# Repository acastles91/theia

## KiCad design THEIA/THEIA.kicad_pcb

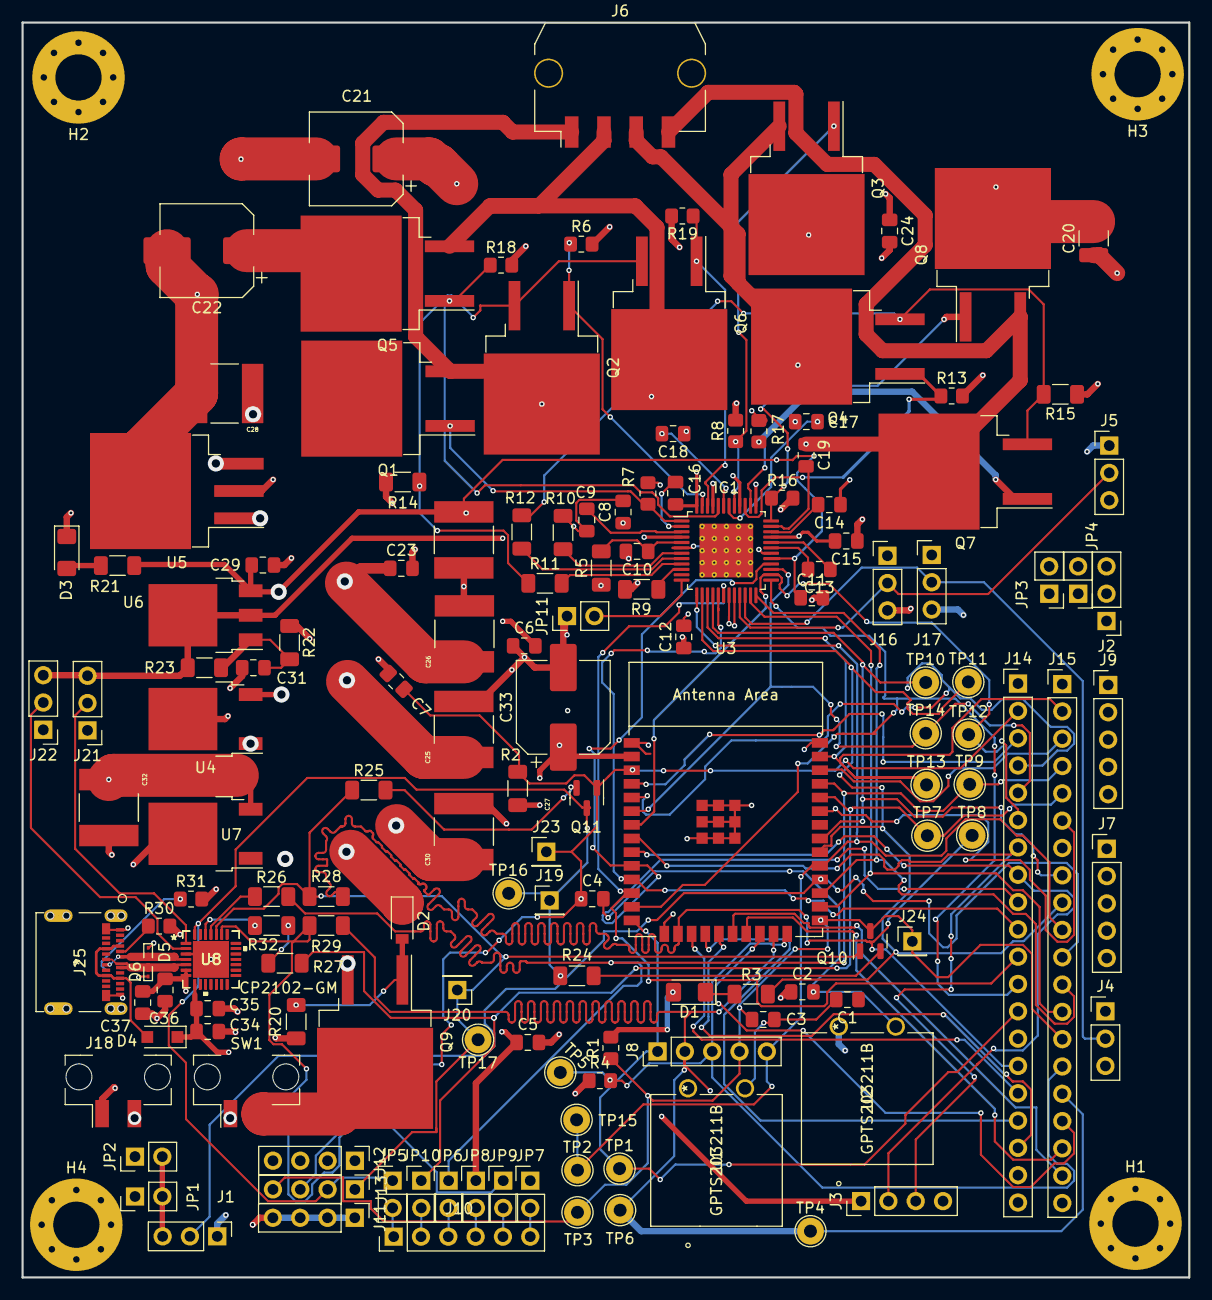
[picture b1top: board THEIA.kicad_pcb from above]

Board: 4 copper layers, 108.5 x 116.7 mm, 154 parts (0 on the bottom side), 103 nets.

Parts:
C1, C2, C6, C8, C12, C14, C15, C16, C17, C18, C19: 0.1uF; C_0805_2012Metric_Pad1.18x1.45mm_HandSolder
C3, C4, C7, C34, C35, C36, C37: 1uF; C_0805_2012Metric_Pad1.18x1.45mm_HandSolder
C5: C22uF; C_0805_2012Metric_Pad1.18x1.45mm_HandSolder
C9, C10: 2.2uF; C_0805_2012Metric_Pad1.18x1.45mm_HandSolder
C11, C23, C24: 0.47uF; C_0805_2012Metric_Pad1.18x1.45mm_HandSolder
C13: 0.022uF; C_0805_2012Metric_Pad1.18x1.45mm_HandSolder
C20: 4.7uF; C_1210_3225Metric_Pad1.33x2.70mm_HandSolder
C21, C22, C33: 22uF; CP_Elec_8x10.5
C25, C26, C27, C28, C30, C32: 22uF; CAPC6153X500N
C29, C31: 10uF; C_0805_2012Metric_Pad1.18x1.45mm_HandSolder
D1, D3: LED_1206_3216Metric_Pad1.42x1.75mm_HandSolder
D2: 10V-Zener; D_SOD-123
D4: 1N5819; D_SOD-123F
D5, D6: ESD9B5.0ST5G; D_SOD-923
H1, H2, H3, H4: MountingHole; MountingHole_4.3mm_M4_Pad_Via
IC1: TMC5160-TA; TQFP-48-1EP_7x7mm_P0.5mm_EP5x5mm_ThermalVias
J1, J2, J4, J5, J21, J22: Conn_01x03_Female; PinHeader_1x03_P2.54mm_Vertical
J3: Conn_01x04_Male; PinHeader_1x04_P2.54mm_Vertical
J6: Conn_01x04_Female; Molex_Micro-Fit_3.0_43650-0410_1x04-1MP_P3.00mm_Horizontal
J7, J9: Conn_01x05_Female; PinHeader_1x05_P2.54mm_Vertical
J8: PinHeader_1x05_P2.54mm_Vertical
J10: PinHeader_1x06_P2.54mm_Vertical
J11, J13: PinHeader_1x04_P2.54mm_Vertical
J12: Conn_01x04_Female; PinHeader_1x04_P2.54mm_Vertical
J14, J15: Conn_01x20_Male; PinHeader_1x20_P2.54mm_Vertical
J16, J17: Conn_01x03_Male; PinHeader_1x03_P2.54mm_Vertical
J18: Conn_01x02_Female; Molex_Micro-Fit_3.0_43650-0221_1x02_P3.00mm_Vertical
J19, J20, J23, J24: PinHeader_1x01_P2.54mm_Vertical
J25: 1054500101
JP1, JP2, JP3, JP4, JP6, JP7, JP8, JP9, JP10, JP11: Jumper_2_Bridged; PinHeader_1x02_P2.54mm_Vertical
JP5: PinHeader_1x02_P2.54mm_Vertical
Q1, Q2, Q3, Q4, Q5, Q6, Q7, Q8: IRLZ44N-SPBF; TO-263-2
Q9: IRF7606PBF; TO-263-2
Q10: S8050; SOT-23
Q11: SOT-23
R1, R4, R30, R31: 5K; R_0805_2012Metric_Pad1.20x1.40mm_HandSolder
R2: R10K; R_1206_3216Metric_Pad1.30x1.75mm_HandSolder
R3: R_1206_3216Metric_Pad1.30x1.75mm_HandSolder
R5: R2.2; R_1206_3216Metric_Pad1.30x1.75mm_HandSolder
R6, R7, R8, R13, R16, R17, R18, R19: R10K; R_0805_2012Metric_Pad1.20x1.40mm_HandSolder
R9, R10, R11, R12: R47; R_1206_3216Metric_Pad1.30x1.75mm_HandSolder
R14, R15: R0.075; R_1206_3216Metric_Pad1.30x1.75mm_HandSolder
R20: R100K; R_1206_3216Metric_Pad1.30x1.75mm_HandSolder
R21: R150K; R_1206_3216Metric_Pad1.30x1.75mm_HandSolder
R22, R26: R0; R_1206_3216Metric_Pad1.30x1.75mm_HandSolder
R23: R3.3K; R_1206_3216Metric_Pad1.30x1.75mm_HandSolder
R24, R25, R32: 10K; R_1206_3216Metric_Pad1.30x1.75mm_HandSolder
R27, R28, R29: 0R; R_1206_3216Metric_Pad1.30x1.75mm_HandSolder
SW1: SW_Push; Molex_Micro-Fit_3.0_43650-0221_1x02_P3.00mm_Vertical
TP1, TP2, TP3, TP4, TP6, TP7, TP8, TP9, TP15: TestPoint; TestPoint_THTPad_D2.5mm_Drill1.2mm
TP5, TP10, TP11, TP12, TP13, TP14, TP16, TP17: TestPoint_THTPad_D2.5mm_Drill1.2mm
U1, U2: GPTS203211B
U3: ESP32-WROOM-E; ESP32-WROOM-32E
U4, U7: TO-252-2
U5: TO-263-3_TabPin2
U6: TO-252-3_TabPin2
U8, U8#2: CP2102-GM

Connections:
5V-LEDS: C32.1, JP2.1 (A), JP4.1 (A), U7.3 (VOUT)
+5V: C11.1, C27.1, C29.1, IC1.29 (VCC), R5.1, R21.2, U4.3 (VOUT), U6.3 (VI)
+12V: C28.1, JP1.1 (A), JP3.1 (A), U5.3 (VOUT)
+24V: C8.1, C14.1, C15.2, C20.2, C21.1, C22.1, C23.1, C24.1, C25.1, C26.1, C30.1, D2.1 (K), IC1.4 (VSA), IC1.33 (VS), Q1.2 (D), Q3.2 (D), Q5.2 (D), Q8.2 (D), Q9.3 (S), U4.1 (VIN), U5.1 (VIN), U7.1 (VIN)
/CLK: IC1.14 (SCK_CFG2), J15.9, R3.2, TP11.1, U3.30 (GPIO18)
/CS: IC1.13 (CSN_CFG3), J8.5, J15.10, TP2.1, TP15.1, U3.29 (GPIO5)
/ESP32/CLK: J15.19, U3.20 (CLK)
/ESP32/CMD: J14.18, U3.19 (CMD)
/ESP32/CTS: JP9.1 (A), R29.2, U8.23 (CTS), U8#2.23 (CTS)
/ESP32/DTR: J13.2, J19.1, JP5.1 (A), Q11.3 (C), R24.1, TP16.1, U8.28 (DTR), U8#2.28 (DTR)
/ESP32/EN: C4.1, C7.1, J13.3, J14.2, J23.1, Q11.1 (E), R2.2, U3.3 (EN/CHIP_PU)
/ESP32/IO0: C3.1, J8.4, J13.4, J15.14, J24.1, Q10.3 (C), R1.1, TP3.1, U3.25 (GPIO0/BOOT/ADC2_CH1)
/ESP32/IO2: J8.3, J15.15, R4.2, TP5.1, U3.24 (ADC2_CH2/GPIO2)
/ESP32/IO4: IC1.23 (ENCB_CFG4), J15.13, U3.26 (ADC2_CH0/GPIO4)
/ESP32/IO12: J8.1, J14.13, TP1.1, U3.14 (MTDI/GPIO12/ADC2_CH5)
/ESP32/IO13: J14.15, R28.1, TP8.1, U3.16 (MTCK/GPIO13/ADC2_CH4)
/ESP32/IO14: IC1.25 (ENCN_CFG6), J14.12, U3.13 (MTMS/GPIO14/ADC2_CH6)
/ESP32/IO15: J8.2, J15.16, R29.1, TP4.1, TP6.1, U3.23 (MTDO/GPIO15/ADC2_CH3)
/ESP32/IO16: IC1.24 (ENCA_CFG5), J15.12, U3.27 (GPIO16)
/ESP32/IO17: J1.2, J15.11, U3.28 (GPIO17)
/ESP32/IO21: J15.6, U3.33 (GPIO21)
/ESP32/IO22: J15.3, U3.36 (GPIO22)
/ESP32/IO25: IC1.28 (DRV_ENN), J14.9, U3.10 (DAC_1/ADC2_CH8/GPIO25)
/ESP32/IO26: IC1.17 (REFL_STEP), J14.10, U3.11 (DAC_2/ADC2_CH9/GPIO26)
/ESP32/IO27: IC1.18 (REFR_DIR), J14.11, U3.12 (ADC2_CH7/GPIO27)
/ESP32/IO32: J3.3, J14.7, U3.8 (32K_XP/GPIO32/ADC1_CH4)
/ESP32/IO33: J3.2, J14.8, U3.9 (32K_XN/GPIO33/ADC1_CH5)
/ESP32/IO34: IC1.27 (DIAG1_SWP), J14.5, TP14.1, U3.6 (GPIO34/ADC1_CH6)
/ESP32/IO35: IC1.26 (DIAG0_SWN), J14.6, TP12.1, U3.7 (GPIO35/ADC1_CH7)
/ESP32/Micro SUB & USB-UART/ACTIVE: U8.11 (*SUSPEND), U8#2.11 (*SUSPEND)
/ESP32/Micro SUB & USB-UART/DCD: J21.2, U8.1 (DCD), U8#2.1 (DCD)
/ESP32/Micro SUB & USB-UART/DSR: U8.27 (DSR), U8#2.27 (DSR)
/ESP32/Micro SUB & USB-UART/RI: J22.2, U8.2 (RI), U8#2.2 (RI)
/ESP32/Micro SUB & USB-UART/RTS: J13.1, J20.1, Q10.1 (E), R25.1, R28.2, TP17.1, U8.24 (RTS), U8#2.24 (RTS)
/ESP32/Micro SUB & USB-UART/RXD: R26.2, U8.25 (RXD), U8#2.25 (RXD)
/ESP32/Micro SUB & USB-UART/TXD: R27.2, R32.2
/ESP32/Micro SUB & USB-UART/USB-D_N: D6.2 (A2), J25.A7 (D1-), J25.B7 (D2-), U8.5 (D-), U8#2.5 (D-)
/ESP32/Micro SUB & USB-UART/USB-D_P: D5.2 (A2), J25.A6 (D1+), J25.B6 (D2+), U8.4 (D+), U8#2.4 (D+)
/ESP32/RXD0: J15.5, JP10.1 (A), R27.1, TP7.1, U3.34 (U0RXD/GPIO3)
/ESP32/SD0: J15.18, U3.21 (SD0)
/ESP32/SD1: J15.17, U3.22 (SD1)
/ESP32/SD2: J14.16, U3.17 (SD2)
/ESP32/SD3: J14.17, U3.18 (SD3)
/ESP32/SENSOR_VN: J14.4, U3.5 (SENSOR_VN/GPIO39/ADC1_CH3)
/ESP32/SENSOR_VP: J14.3, U3.4 (SENSOR_VP/GPIO36/ADC1_CH0)
/ESP32/TXD0: J15.4, JP6.1 (A), R26.1, TP9.1, U3.35 (U0TXD/GPIO1)
/MISO: IC1.16 (SDO_CFG0), J15.8, TP10.1, U3.31 (GPIO19)
/MOSI: IC1.15 (SDI_CFG1), J15.2, TP13.1, U3.37 (GPIO23)
/TMC5160-SMD/BLACK: C18.1, IC1.45 (BMB2), J6.2, Q5.3 (S), Q6.2 (D)
/TMC5160-SMD/BLUE: C17.1, IC1.40 (BMA1), J6.3, Q3.3 (S), Q4.2 (D)
/TMC5160-SMD/CLK: IC1.12 (CLK), JP11.2 (B)
/TMC5160-SMD/GREEN: C16.1, IC1.48 (BMB1), J6.1, Q1.3 (S), Q2.2 (D)
/TMC5160-SMD/RED: C19.1, IC1.37 (BMA2), J6.4, Q7.2 (D), Q8.3 (S)
/TMC5160-SMD/SD_MODE: IC1.21 (SD_MODE), J5.2, J16.2
/TMC5160-SMD/SPI_MODE: IC1.22 (SPI_MODE), J4.2, J17.2
EXT_5V: C34.2, C35.2, D4.1 (K), J14.19, U8.8 (VBUS), U8#2.8 (VBUS)
unnamed: C1.2, C3.2, U1.6
unnamed: C2.2, C4.2, U2.6
unnamed: C9.1, IC1.3 (12VOUT)
unnamed: C10.1, IC1.5 (5VOUT), R5.2
unnamed: C13.1, IC1.32 (CPI)
unnamed: C13.2, IC1.31 (CPO)
unnamed: C14.2, IC1.34 (VCP)
unnamed: C16.2, IC1.2 (CB1)
unnamed: C17.2, IC1.42 (CA1)
unnamed: C18.2, IC1.43 (CB2)
unnamed: C19.2, IC1.35 (CA2)
unnamed: C31.1, R22.2, R23.2, U6.1 (GND)
unnamed: D1.1 (K), R3.1
unnamed: D2.2 (A), Q9.1 (G), R20.1
unnamed: D3.2 (A), R21.1
unnamed: D4.2 (A), J25.A4 (VBUS1), J25.A9 (VBUS2), J25.B4 (VBUS3), J25.B9 (VBUS4)
unnamed: IC1.1 (HB1), Q1.1 (G), R7.1
unnamed: IC1.7 (SRAL), R10.2
unnamed: IC1.8 (SRAH), R12.2
unnamed: IC1.9 (SRBH), R11.2
unnamed: IC1.10 (SRBL), R9.2
unnamed: IC1.36 (HA2), Q8.1 (G), R16.1
unnamed: IC1.38 (LA2), Q7.1 (G), R17.1
unnamed: IC1.39 (LA1), Q4.1 (G), R13.1
unnamed: IC1.41 (HA1), Q3.1 (G), R8.1
unnamed: IC1.44 (HB2), Q5.1 (G), R18.1
unnamed: IC1.46 (LB2), Q6.1 (G), R19.1
unnamed: IC1.47 (LB1), Q2.1 (G), R6.1
unnamed: J1.3, JP1.2 (B), JP2.2 (B)
unnamed: J2.3, JP3.2 (B), JP4.2 (B)
unnamed: J10.1, JP5.2 (B)
unnamed: J10.2, JP10.2 (B)
unnamed: J10.3, JP6.2 (B)
unnamed: J10.4, JP8.2 (B)
unnamed: J10.5, JP9.2 (B)
unnamed: J10.6, JP7.2 (B)
unnamed: J25.A5 (CC1), R30.1
unnamed: J25.B5 (CC2), R31.1
unnamed: Q2.3 (S), Q6.3 (S), R11.1, R14.2
unnamed: Q4.3 (S), Q7.3 (S), R12.1, R15.2
unnamed: Q9.2 (D), SW1.2
unnamed: Q10.2 (B), R24.2
unnamed: Q11.2 (B), R25.2
unnamed: R32.1, U8.26 (TXD), U8#2.26 (TXD)
POWER-IN+: J18.2, SW1.1
POWER-IN-: C1.1, C2.1, C5.2, C6.1, C7.2, C8.2, C9.2, C10.2, C11.2, C12.2, C15.1, C20.1, C21.2, C22.2, C23.2, C24.2, C25.2, C26.2, C27.2, C28.2, C29.2, C30.2, C31.2, C32.2, C33.2, C34.1, C35.1, C36.2, C37.2, D3.1 (K), D5.1 (A1), D6.1 (A1), IC1.6 (GNDA), IC1.11 (TST_MODE), IC1.19 (GNDD), IC1.30 (GNDD_2), IC1.49 (GNDP), J1.1, J2.1, J3.4, J4.1, J5.1, J7.1, J7.2, J7.3, J7.4, J7.5, J11.1, J11.2, J11.3, J11.4, J14.14, J15.1, J15.7, J16.3, J17.3, J18.1, J21.1, J22.1, J25.A1 (GND1), J25.A12 (GND2), J25.B1 (GND3), J25.B12 (GND4), JP7.1 (A), JP11.1 (A), R4.1, R6.2, R7.2, R8.2, R9.1, R10.1, R13.2, R14.1, R15.1, R16.2, R17.2, R18.2, R19.2, R20.2, R22.1, R30.2, R31.2, U1.1, U2.1, U3.1 (GND), U3.15 (GND), U3.38 (GND), U3.39 (GND_THERMAL), U4.2 (GND), U5.2 (GND), U7.2 (GND), U8.3 (GND), U8.29 (EPAD), U8#2.3 (GND), U8#2.29 (EPAD)
VDD33: C5.1, C6.2, C12.1, C33.1, C36.1, C37.1, D1.2 (A), IC1.20 (VCC_IO), J3.1, J4.3, J5.3, J9.1, J9.2, J9.3, J9.4, J9.5, J12.1, J12.2, J12.3, J12.4, J14.1, J16.1, J17.1, J21.3, J22.3, JP8.1 (A), R1.2, R2.1, R23.1, U3.2 (3V3), U6.2 (VO), U8.6 (VDD), U8.7 (REGIN), U8#2.6 (VDD), U8#2.7 (REGIN)

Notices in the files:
parts and their libraries:
Copyright 2021 Accelerated Designs. All rights reserved.
